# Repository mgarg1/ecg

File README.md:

ECG
===

An electrocardiograph prototype for the Remote Neonatal Monitoring and Intervention Project.

Dependencies
------------

- Python 2.7
- Arduino >= 1.5.6-r2 (for Arduino Due)
- stream-plot (source included, but streamplot's dependencies need to be met) - https://github.com/s-gv/stream-plot
- MATLAB / Octave if you want to run simulations
- TI SmartRF Flash Programmer
- IAR 8051 >= 8.30 (only if you want to re-compile the source code for CC2540)
- TI CCDebugger (for programming CC2540)

How-to-use
----------

Wired ECG with Arduino:

- Build the circuit in `schematics/ecg_arduino.png`. A USB to UART converter such as FT232 or CP2102 may be used.
- Program the Arduino with the source in `ecg_arduino/ecg_arduino.ino`.
- Goto `ecg_visualizer_arduino_PC/` and run `python visualizer.py`. If the serial port name is incorrect, edit `visualizer.py`.
- Press the hi-z electrodes across the heart and press the RLD electrode to the leg or forehead. Alternatively, the outer ring of one of the hi-z electrodes can be connected to the RLD electrode. For more details, see the technical report in `report/ecg_tech_report.pdf`. You should now see an ECG signal on the PC display.
- Note that a laptop (with the power cord removed) must be used to power the Arduino. Preferably, keep the laptop on your lap. Interference will be much worse if a mains powered desktop is used; the interference may be so strong as to saturate the amplifiers leading to no useful ECG signal at all.

Wireless ECG with Bluetooth Low Energy (BLE using CC2540):

- Build the circuit in `schematics/ecg_CC2540.png`. A more complete schematic is in `schematics/ecg_CC2540_full.png`. Program the CC2540 in the circuit with the hex file `ecg_CC2540/hexfiles/SimpleBLEPeripheral.hex`.
- Connect the CC2540 USB dongle to a PC (either a laptop or a mains powered desktop will do). Program the CC2540 USB dongle with the hex file `ecg_CC2540/hexfiles/CC2540_SmartRF_HostTestRelease_All.hex`.
- Goto `ecg_visualizer_ble_PC/` and run `python visualizer.py`. If the serial port name is incorrect, edit `visualizer.py`.
- Press the hi-z electrodes across the heart and press the RLD electrode to the leg or forehead. Alternatively, the outer ring of one of the hi-z electrodes can be connected to the RLD electrode. For more details, see the technical report in `report/ecg_tech_report.pdf`. You should now see an ECG signal on the PC display. A sample recording may be found [here](https://github.com/s-gv/ecg/blob/master/data/ble_single_battery_LP5907_psuedo2_RLD/screenshots/screenshot0.png).
- Note that the CC2540, which is gathering ECG data and transmitting wirelessly, has to be powered by a battery (ex: CR2032 coin cell). If a mains power source is used, interference will be much worse.

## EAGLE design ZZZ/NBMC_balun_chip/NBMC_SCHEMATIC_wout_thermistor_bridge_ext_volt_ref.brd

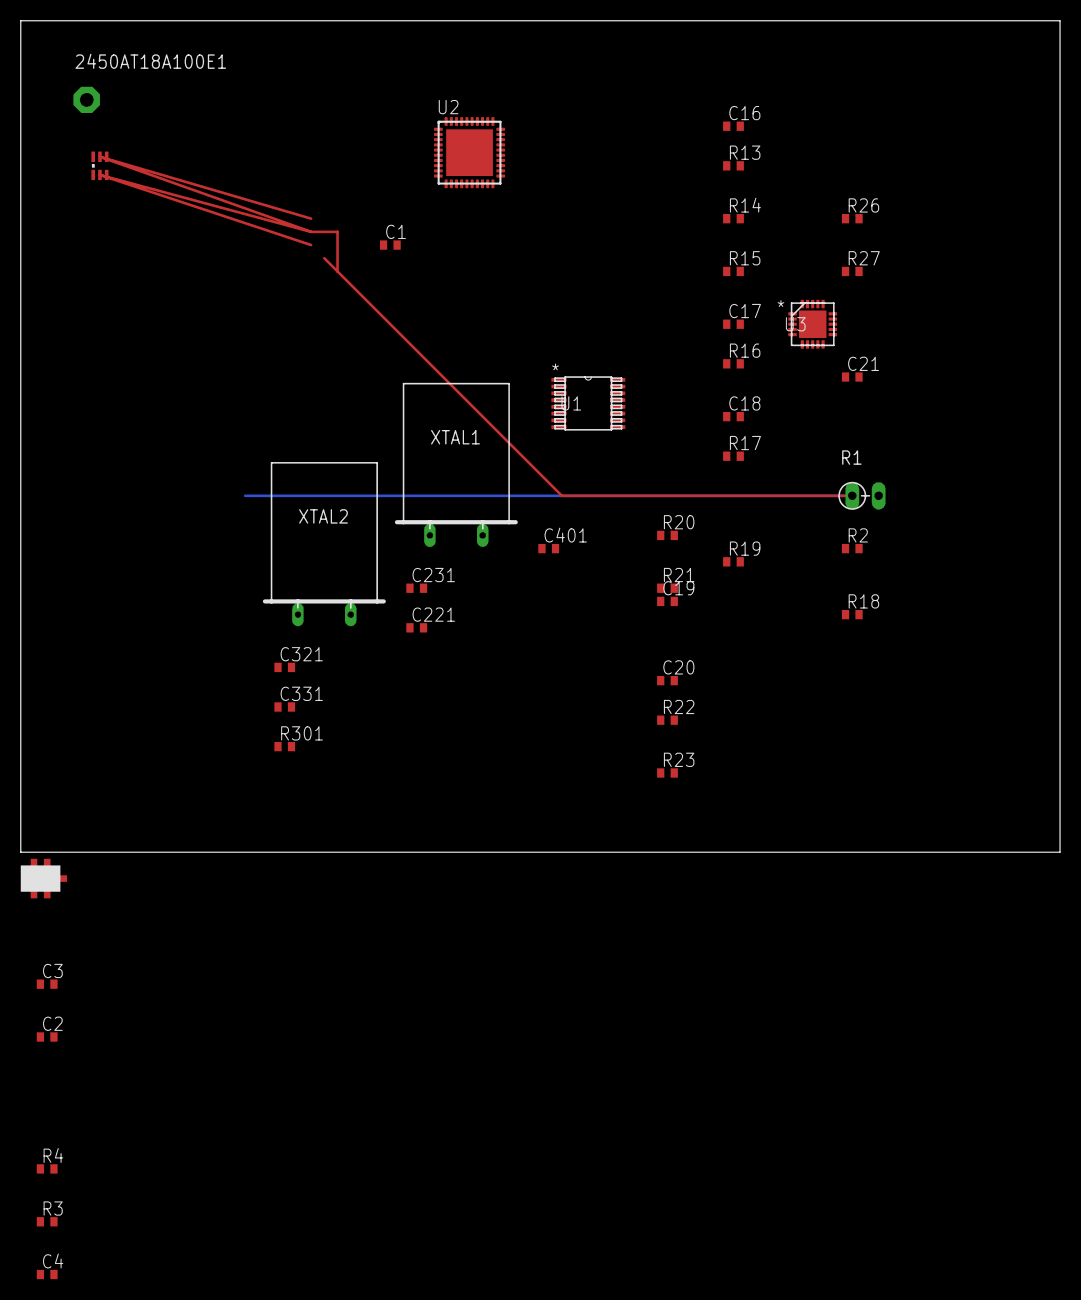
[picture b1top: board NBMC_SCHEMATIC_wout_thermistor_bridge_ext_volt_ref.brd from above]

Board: 2 copper layers, 100.0 x 80.0 mm, 41 parts (0 on the bottom side), 38 nets.

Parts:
2450AT18A100E1: Ant Chip; PAD-01
C1, C401: 1µF; C0402
C2, C4: 20µF; C0402
C3: 10µF; C0402
C16: 10nF; C0402
C17, C18: 0.1µF; C0402
C19: 1.5nF; C0402
C20: 1nF; C0402
C21: 0.33µF; C0402
C221, C231: 12pF; C0402
C321, C331: 15pF; C0402
R1: THERMISTOR-2,5; RS-2,5
R2: 0Ω; R0402
R3: 1.15MΩ; R0402
R4: 0.1MΩ; R0402
R13: 100kΩ; R0402
R14, R20, R21: 1MΩ; R0402
R15, R16, R17, R18, R26, R27: 10MΩ; R0402
R19: 1.4MΩ; R0402
R22, R23: 180kΩ; R0402
R301: 56KΩ; R0402
U1: ADG709BRU; RU_16
U2: CC2541; RHA_S-PVQFN-N40
U3: AD8232ACPZ_R7; CP_20_10
U4: 2450BM15A0002
U$1: LM4121; 0402
XTAL1: 32MHz; Q
XTAL2: 32.768kHz; Q

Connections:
GND: C1.1, C2.1, C3.1, C4.2, C17.1, C18.1, C221.1, C231.1, C321.2, C331.2, C401.1, R1.1, R3.1, R16.1, R301.1, U1.3, U1.11, U1.12, U1.13, U1.15, U2.1, U2.EXP, U3.14, U3.16, U3.21, U4.2, U4.5, U4.6, U$1.P$2
unnamed: U2.26, U4.3
unnamed: R301.2, U2.30
unnamed: C1.2, U2.20
unnamed: U2.25, U4.4
unnamed: R4.2, U$1.P$5
unnamed: 2450AT18A100E1.1, U4.1
unnamed: C401.2, U2.40
unnamed: R2.2, U1.9
unnamed: R1.2, R2.1, U2.19
unnamed: C221.2, U2.22, XTAL1.2
unnamed: C231.2, U2.23, XTAL1.1
unnamed: C321.1, U2.32, XTAL2.2
unnamed: C331.1, U2.33, XTAL2.1
unnamed: R22.1, U3.2
unnamed: R3.2, R4.1, U2.12
unnamed: C20.1, R26.1, R27.1, U3.5
unnamed: U1.1, U2.6
unnamed: U1.16, U2.7
unnamed: R23.1, U3.3
unnamed: R19.1, U3.6
unnamed: U2.11, U3.11
unnamed: U2.9, U3.12
unnamed: U2.8, U3.13
unnamed: C19.2, R20.2, R21.1
unnamed: R22.2, R27.2
unnamed: R13.1, R14.2, U3.9
unnamed: R23.2, R26.2
unnamed: C16.2, R20.1, U3.7
unnamed: C16.1, R13.2, U3.8
unnamed: C19.1, R14.1, U2.13, U3.10
unnamed: C18.2, R15.2, R16.2, U3.18
unnamed: R18.2, R21.2, U3.19
unnamed: C21.1, R17.2, U3.20
unnamed: R17.1, R18.1, R19.2
unnamed: C20.2, U3.4
unnamed: C21.2, U3.1
VSS: C2.2, C3.2, C4.1, C17.2, R15.1, U1.2, U1.14, U2.10, U2.21, U2.24, U2.27, U2.28, U2.29, U2.31, U2.39, U3.15, U3.17, U$1.P$3, U$1.P$4

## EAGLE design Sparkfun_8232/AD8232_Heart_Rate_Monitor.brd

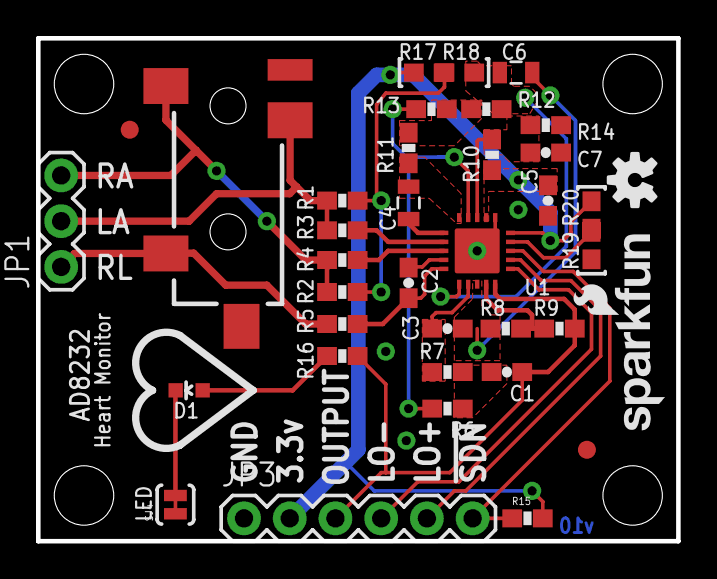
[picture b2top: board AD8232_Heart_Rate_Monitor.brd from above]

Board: 2 copper layers, 35.6 x 27.9 mm, 42 parts (0 on the bottom side), 27 nets.

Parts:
C1: 1.5nF; 0603-CAP
C2: 1nF; 0603-CAP
C3: 10nF; 0603-CAP
C4, C6: 0.33uF; 0805
C5: 0.1uF; 0603-CAP
C7: 0.1uf; 0603-CAP
D1: RED; LED-0603
FID1, FID2: FIDUCIAL1X2; FIDUCIAL-1X2
FRAME1: FRAME-LETTER; CREATIVE_COMMONS
JP1: 1X03
JP2: AUDIO-JACK-3.5MM-SMD
JP3: 1X06
LOGO1: OSHW-LOGOS; OSHW-LOGO-S
LOGO2: SFE_LOGO_NAME_FLAME.1_INCH; SFE_LOGO_NAME_FLAME_.1
R1, R2, R10, R11, R13, R14: 10M; 0603-RES
R3, R4: 180k; 0603-RES
R5: 360k; 0603-RES
R6, R7, R9: 1M; 0603-RES
R8: 100k; 0603-RES
R12: 1.4M; 0603-RES
R15: 10K; 0603-RES
R16: 1k; 0603-RES
R17, R19: 0; 0603
R18, R20: DNP; 0603
SJ4: LED DISABLE; SJ_2S-TRACE
STANDOFF1, STANDOFF2, STANDOFF3, STANDOFF4: STAND-OFF
U1: AD8232; LFCSP_20

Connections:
3.3V: C5.1, JP3.2, R10.1, R15.2, R17.1, R20.2, U1.15, U1.17
GND: C5.2, C7.2, JP3.1, R14.1, R19.1, SJ4.1, U1.16, U1.PAD
LA: JP1.2, JP2.RING, R1.1, R3.1
LO+: JP3.5, U1.12
LO-: JP3.4, U1.11
unnamed: R3.2, U1.2
unnamed: R4.2, U1.3
unnamed: C3.2, R7.2, U1.7
unnamed: C4.2, R11.1, U1.20
unnamed: C7.1, R10.2, R14.2, U1.18
unnamed: D1.A, R16.1
unnamed: R8.1, R9.2, U1.9
unnamed: R6.2, R13.1, U1.19
unnamed: C1.2, R6.1, R7.1
unnamed: D1.C, SJ4.2
unnamed: R19.2, R20.1, U1.14
unnamed: C4.1, U1.1
unnamed: R11.2, R12.1, R13.2
unnamed: C6.1, R12.2, R18.2, U1.6
unnamed: C2.1, U1.4
unnamed: C2.2, R5.1, U1.5
unnamed: R1.2, R2.2, R17.2, R18.1
RA: JP1.3, JP2.SLEEVE, R2.1, R4.1
REFOUT: C3.1, C6.2, R8.2, U1.8
RL: JP1.1, JP2.TIP, R5.2
SDN: JP3.6, R15.1, U1.13
SIGNAL_OUT: C1.1, JP3.3, R9.1, R16.2, U1.10

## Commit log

2014-03-03 Added README
2014-03-03 MIT License
2014-03-03 hello world with serial link
2014-03-05 Visualizer working
2014-03-05 Dependencies
2014-03-05 removed empty module
2014-03-05 ignoring temp files
2014-03-05 Ignore *.swp
2014-03-05 Visualizer with square wave from Arduino
2014-03-05 removed swp file
2014-03-05 Visualizing saw tooth wave
2014-03-17 sine wave generation
2014-03-17 Constant DC
2014-03-17 Amplitude Phase control from keyboard working
2014-03-18 DAC1 is set to VDD/2
2014-03-18 removed pyc files
2014-03-30 Modeling Body and ECG Ckt in MATLAB
2014-03-31 Modeled noise in ADC
2014-03-31 Models DAC
2014-03-31 Models attenuator
2014-03-31 Fixed clipping
2014-03-31 DC Amplifier model
2014-03-31 Status msg and MATLAB dependency
2014-03-31 Added Galry's LICENSE file
2014-03-31 Testing full signal chain without body model
2014-03-31 Phase detector and NCO working individually
2014-04-02 Trying out FFT for PLL
2014-04-02 DFT to find freqs. Doesn't work well for fractional freqs
2014-04-03 Trying 50 Hz notch filter
2014-04-03 Getting amplitude from PLL
2014-04-04 Changed License to AGPL for compatibility
2014-04-08 MIT-BIH ECG data for simulation
2014-04-08 Minor fix
2014-04-09 Synthesized ecg data
2014-04-15 Working software PLL
2014-04-15 Removed useless files
2014-05-01 Martens' simple PLL not working
2014-05-01 Fixed bug. Martens' PLL without error filtering and adaptation suppression works
2014-05-01 Step input interference
2014-05-01 Amplitude step and frequency step
2014-05-01 Bug fix: Amplitude_estimate > 0
2014-05-01 Martens' PLL with error works but has quirks
2014-05-02 Bug fix: Error filter cutoff freq
2014-05-02 Minor fix about not implementing adaptation blocking
2014-05-02 Bug fix: estimates were 0 when estimation was suppressed
2014-05-02 Manual adaptation suppression
2014-05-02 Demonstrating the difficulty of auto suppression
2014-05-04 potential benefits
2014-05-05 TODO: Detect if PLL is in lock
2014-05-05 Marten's PLL working
2014-05-05 Test on MIT-BIH database
2014-05-05 ADC Resolution
2014-05-12 minor re-organization
2014-05-12 Real recordings
2014-05-13 one more data point
2014-05-13 Another data point
2014-05-15 Data from Faraday cage in GB's lab
2014-05-15 Recording conditions
2014-05-15 Adaptive applied to the data acquired in faraday cage
2014-05-16 ADC resolution is now 12 bits
2014-05-16 Added ADC resolution and sample rate
2014-05-16 Data for custom 3 electrode (dry) board
2014-05-16 ADC resolution 12 bits
2014-05-16 psuedo 2 electrode
2014-05-16 Adaptive filter screenshots
2014-05-16 Filtering psuedo 2-electrode data
2014-05-19 Data for single ended electrode
2014-05-19 input set to single ended 2 electrode config
2014-05-19 Screenshots of adaptive filtering in action
2014-05-19 One more screenshot of adaptive filtering in action
2014-05-19 2 electrode diff. with entire circuit and laptop on my lap
2014-05-19 One more data point with lappy on lap
2014-05-19 working on diff amp with floating ground with lappy on lap
2014-05-19 adaptive filtering on diff. amp with lappy on lap
2014-05-20 Psuedo 2-electrode with RLD
2014-05-25 Renamed project
2014-05-31 removed two large screenshots
2014-05-31 BLE Host (PC) side visuablizer
2014-05-31 Renamed screenshot files to keep windows happy
2014-05-31 BLE CC2540
2014-05-31 Renamed PC visualizer
2014-05-31 Applied AGPL license
2014-05-31 Commented out code related to software-defined-ecg
2014-05-31 Arduino schematic added
2014-06-03 New Python BLE Module
2014-06-03 Log messages
2014-06-04 Method to change connection intervals
2014-06-04 Removed old project files
2014-06-04 New BLE 1.4 based ECG project
2014-06-04 Change connection interval before making connection
2014-06-04 Terminate all links during BTDongle Init
2014-06-04 Timer interrupt works but sampling is irregular
2014-06-04 2 ms sampling works with around 10% jitter
2014-06-04 Working with 2.5 ms tick
2014-06-05 ADC seems to work
2014-06-05 Removed unnecessary wait in BTInit()
2014-06-05 converting raw vals to 16-bit ADC readings
2014-06-05 ECG visualizer working with BLE
2014-06-05 Data from BLE based pseudo-2-RLD ECG
2014-06-05 Checking if GAPInit() succeeded
2014-06-05 Genericized length of Char4
2014-06-06 CR2032 battery test
2014-06-09 Single battery CR2032 with REF3320
2014-06-11 Initial long term recordings
2014-06-11 Save all data to disk
2014-06-11 More data from belt
2014-06-12 renamed files
2014-06-12 added length checks to prevent crashes in long runs
2014-06-24 ADC reference from outside
2014-06-24 Binary files
2014-06-26 fixed streamplot
2014-06-26 data with LP5907
2014-06-27 Screenshots demoing noise due to IR drop
2014-06-27 fixed RLD gain
2014-06-27 Long term recording with belt
2014-06-27 minor change
2014-06-27 Passive dry ground with belt
2014-06-27 changed new pins to analog mode
2014-06-30 How-to-use instructions
2014-06-30 CC2540 sch
2014-06-30 mentioned hi-z when talking about pseudo 2-electrodes
2014-06-30 Added two dots
2014-07-01 Link to figure
2014-07-01 Tech report
2014-07-03 Complete schematic with antenna matching network
2014-07-03 Removed blank matching network
2014-07-24 CR2032 BLE with PDMS layer
2014-08-15 Renamed to USB Dongle
2014-08-21 Updated Tech Report
2014-08-29 Haynes test done
2014-11-25 intial commit
2014-11-25 intial commit2
2014-11-25 added testpoints ,100uf cap, cap across thermistor,JP2,removed battery and battery holder connection proper
2014-11-26 added schematic image
2014-11-26 updated BOM with the new changes of TP,100uF cap etc
2014-12-05 reset filter is added, Thermistor removed and the testpoint connections to the JP1 are removed
2014-12-18 mouser BOM added and ordered
2015-01-16 Files to Be used for nbmc project
2015-01-17 Initial Commit - Added All files from everywhere
    Python Scripts from Ubuntu and 3 android projects - RedBearLab,
    AndroidDevBLE, AndroidPlot
2015-01-18 Android Project Added
2015-01-18 Moved ecg_schematic under ZZZ
2015-01-18 Merging of ecg_schematic complete
    Schematic files moved under the same repository and all unused data is
    removed

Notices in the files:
parts and their libraries:
SparkFun-Aesthetics: Licensing: CC v3.0 Share-Alike You are welcome to use this library for commercial purposes.
SparkFun-Aesthetics: Released under the Creative Commons Attribution Share-Alike 3.0 License
SparkFun-Aesthetics: http://creativecommons.org/licenses/by-sa/3.0
